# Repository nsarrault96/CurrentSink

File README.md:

# CurrentSink
My version of the Current Sink or Swim project from Contextual Electronics

<br/>

## Component Selection

### Op Amp<br/>
**Part Number:** MCP6002

<br/>

### Voltage Regulator<br/>
**Part Number:** MIC5205

<br/>

### Mosfet<br/>
**Part Number:** STP55FN06L

<br/>

### Heatsink<br/>
**Part Number:** 529702B02500G

<br/>

### Current Sense Resistor<br/>

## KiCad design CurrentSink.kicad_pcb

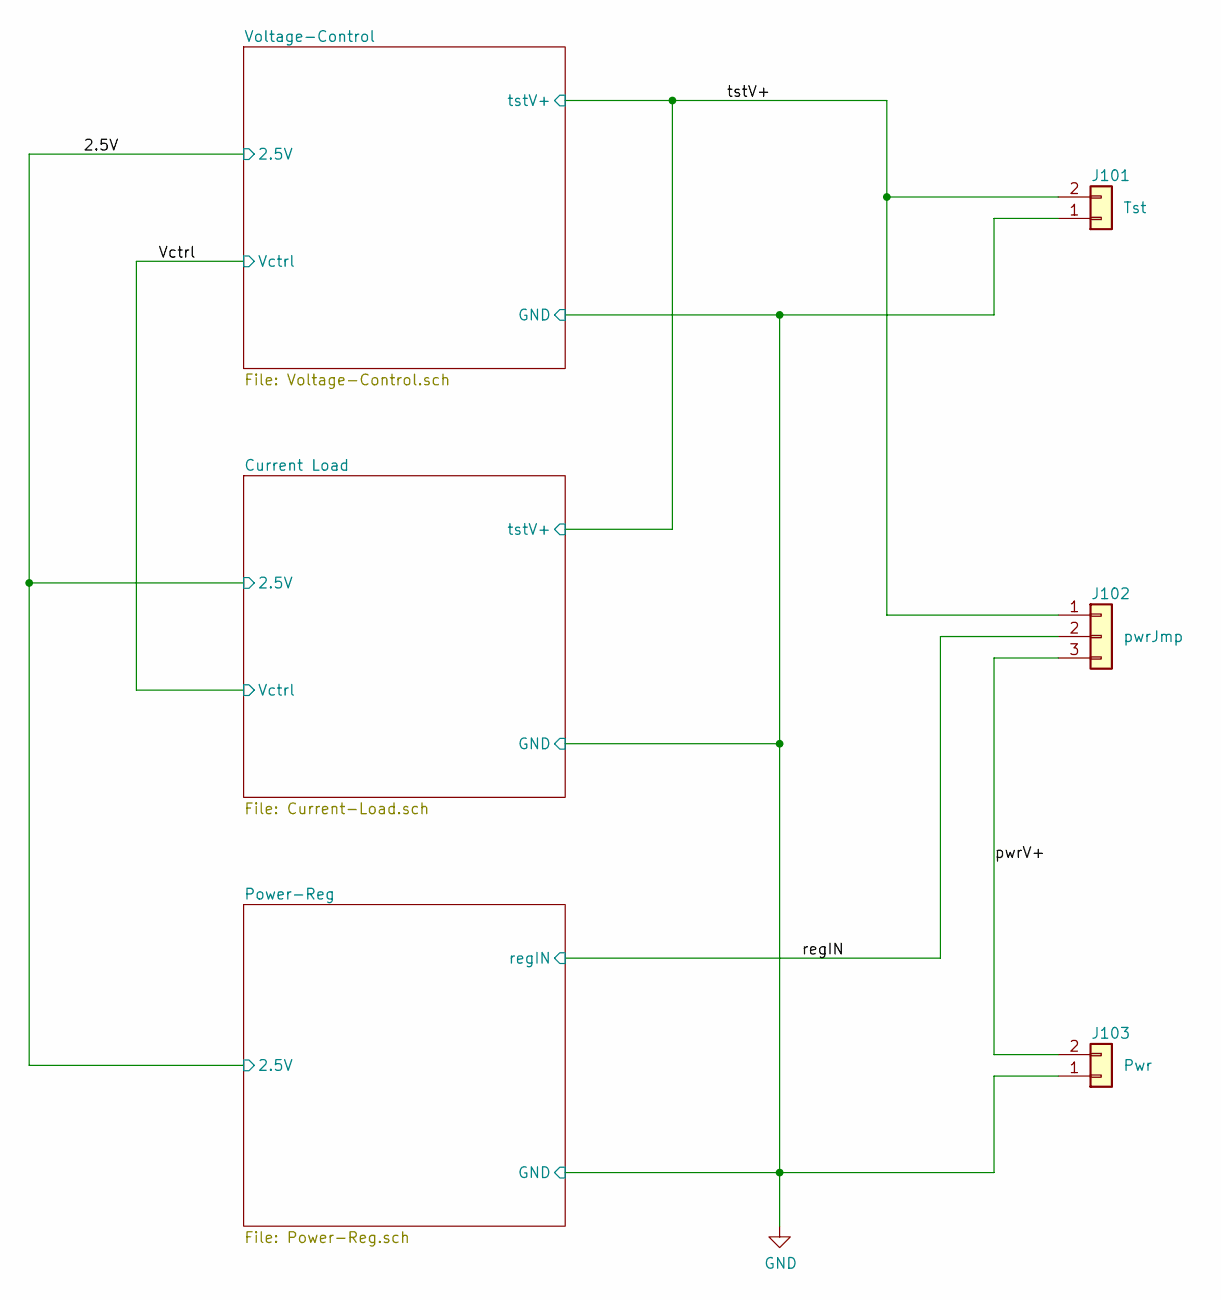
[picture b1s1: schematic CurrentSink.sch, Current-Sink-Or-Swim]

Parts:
J101: Tst; TerminalBlock_Phoenix_PT-1,5-2-3.5-H_1x02_P3.50mm_Horizontal; MPN 1984617
J102: pwrJmp; PinHeader_1x03_P1.27mm_Vertical
J103: Pwr; TerminalBlock_Phoenix_PT-1,5-2-3.5-H_1x02_P3.50mm_Horizontal; MPN 1984617

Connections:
/pwrV+: J102.3, J103.2
/regIN: J102.2; also elsewhere on the board
/tstV+: J101.2, J102.1; also elsewhere on the board
GND: J101.1, J103.1; also elsewhere on the board

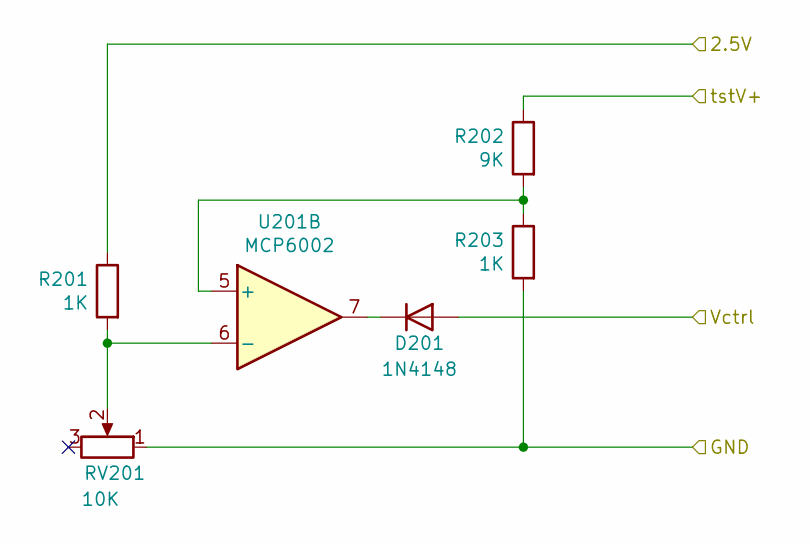
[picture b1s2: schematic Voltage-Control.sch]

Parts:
D201: 1N4148; D_SOD-123
R201, R203: 1K; R_0603_1608Metric_Pad0.98x0.95mm_HandSolder
R202: 9K; R_0603_1608Metric_Pad0.98x0.95mm_HandSolder
RV201: 10K; POT_TTElect_P160KN; MPN P160KN-0QD15B10K
U201: MCP6002; SOIC-8_3.9x4.9mm_P1.27mm; MPN MCP6002T-I/SN

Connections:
/2.5V: R201.1; also elsewhere on the board
/Vctrl: D201.2 (A); also elsewhere on the board
/tstV+: R202.1; also elsewhere on the board
GND: R203.2, RV201.1; also elsewhere on the board
unnamed: D201.1 (K), U201.7
unnamed: R201.2, RV201.2, U201.6 (-)
unnamed: R202.2, R203.1, U201.5 (+)

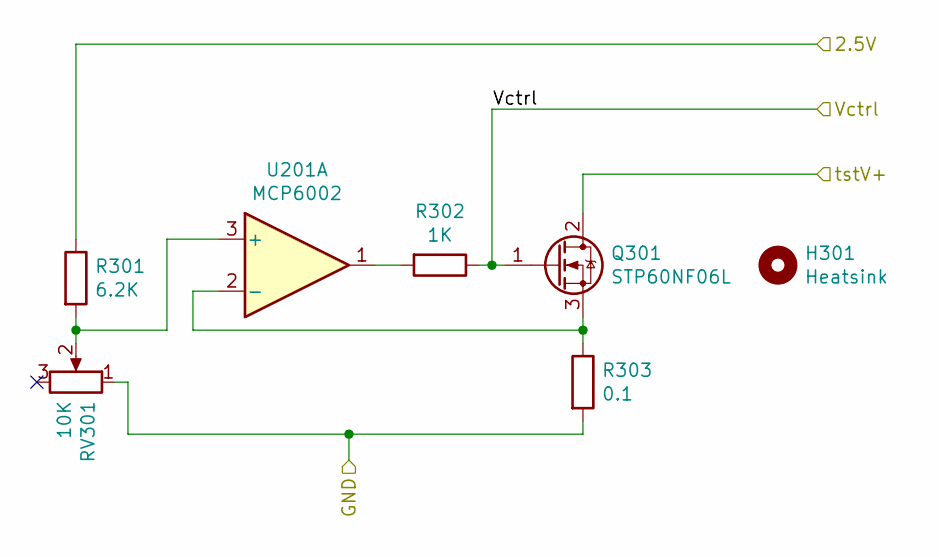
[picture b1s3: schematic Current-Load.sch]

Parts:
H301: Heatsink; MPN 529802B02500G
Q301: STP60NF06L; TO-220-3_Vertical; MPN STP60NF06L
R301: 6.2K; R_0603_1608Metric_Pad0.98x0.95mm_HandSolder
R302: 1K; R_0603_1608Metric_Pad0.98x0.95mm_HandSolder
R303: 0.1; R_2512_6332Metric_Pad1.40x3.35mm_HandSolder; MPN CRA2512-FZ-R100ELF
RV301: 10K; POT_TTElect_P160KN; MPN P160KN-0QD15B10K
U201: MCP6002; SOIC-8_3.9x4.9mm_P1.27mm; MPN MCP6002T-I/SN

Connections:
/2.5V: R301.1; also elsewhere on the board
/Vctrl: Q301.1 (G), R302.1; also elsewhere on the board
/tstV+: Q301.2 (D); also elsewhere on the board
GND: R303.2, RV301.1; also elsewhere on the board
unnamed: Q301.3 (S), R303.1, U201.2 (-)
unnamed: R301.2, RV301.2, U201.3 (+)
unnamed: R302.2, U201.1

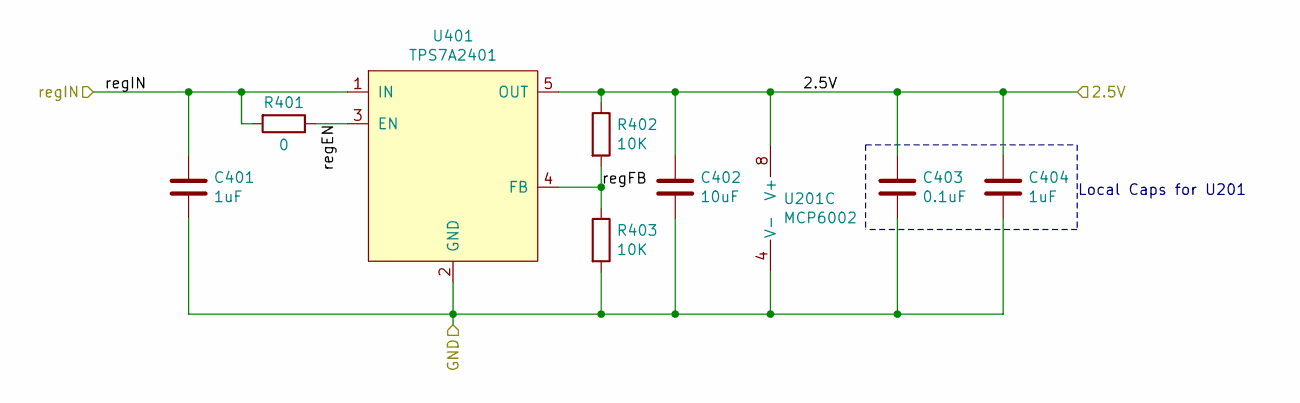
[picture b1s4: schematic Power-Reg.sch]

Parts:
C401, C404: 1uF; C_0603_1608Metric_Pad1.08x0.95mm_HandSolder
C402: 10uF; C_0603_1608Metric_Pad1.08x0.95mm_HandSolder
C403: 0.1uF; C_0603_1608Metric_Pad1.08x0.95mm_HandSolder
R401: 0; R_0603_1608Metric_Pad0.98x0.95mm_HandSolder
R402, R403: 10K; R_0603_1608Metric_Pad0.98x0.95mm_HandSolder
U201: MCP6002; SOIC-8_3.9x4.9mm_P1.27mm; MPN MCP6002T-I/SN
U401: TPS7A2401; SOT-23-5_HandSoldering; MPN TPS7A2401DBVR

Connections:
/2.5V: C402.1, C403.1, C404.1, R402.1, U201.8 (V+), U401.5 (OUT); also elsewhere on the board
/Power-Reg/regEN: R401.1, U401.3 (EN)
/Power-Reg/regFB: R402.2, R403.1, U401.4 (FB)
/regIN: C401.1, R401.2, U401.1 (IN); also elsewhere on the board
GND: C401.2, C402.2, C403.2, C404.2, R403.2, U201.4 (V-), U401.2 (GND); also elsewhere on the board

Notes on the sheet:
Local Caps for U201

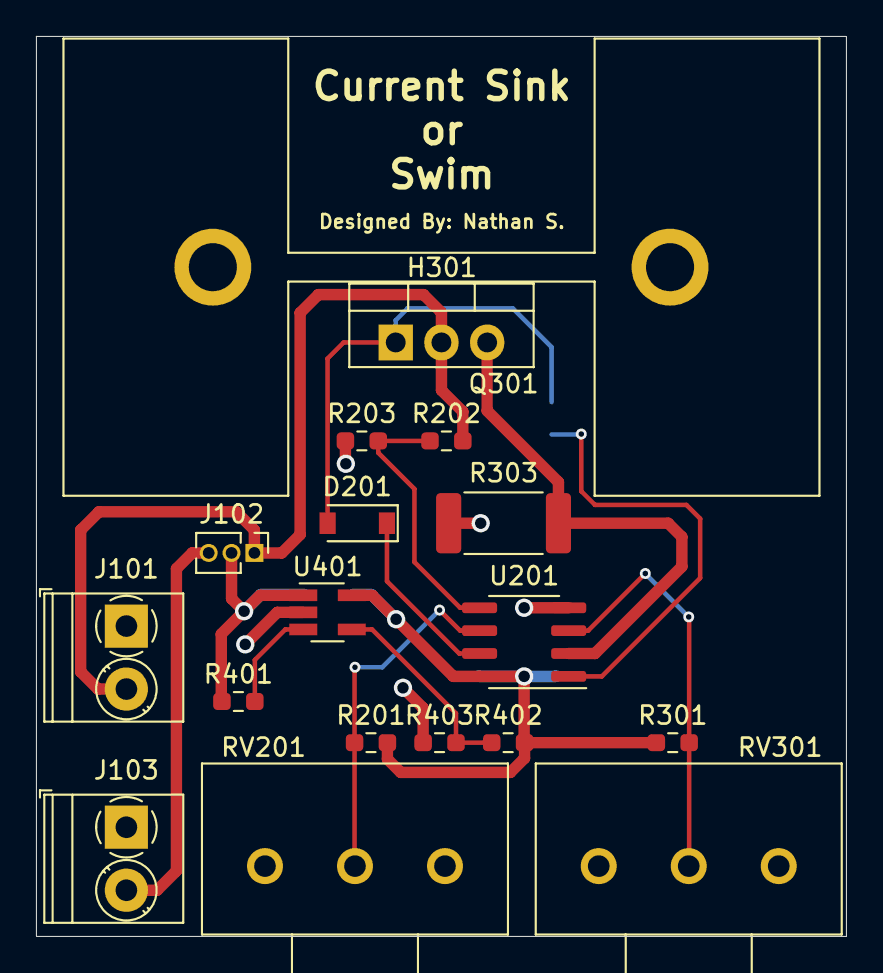
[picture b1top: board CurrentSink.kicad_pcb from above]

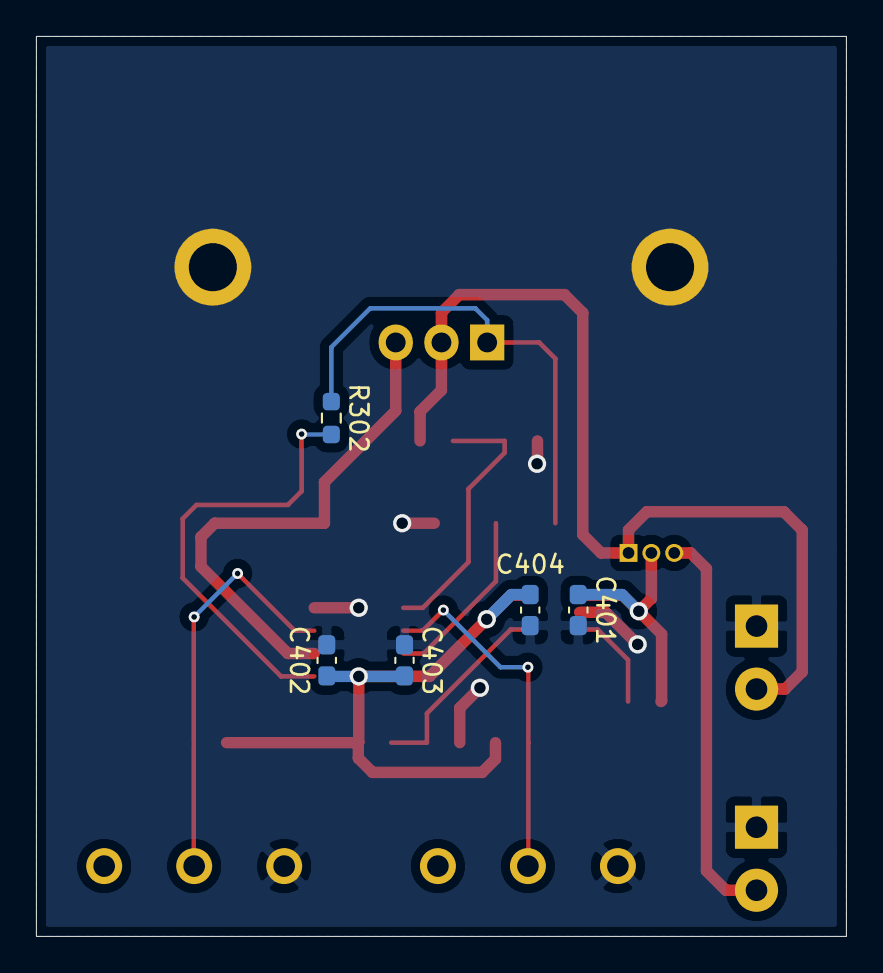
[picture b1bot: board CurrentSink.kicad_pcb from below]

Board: 2 copper layers, 45.0 x 50.0 mm, 23 parts (5 on the bottom side), 14 nets.

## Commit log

2021-01-19 Adding all Kicad files & folders for the project
2021-01-19 Add Component Selection Section
    Initial add of the component selection information to the readme file
2021-01-19 Fix breaks
2021-01-20 Adding the beginning schematic and Datasheets
2021-01-25 Updating the Schematic
2021-02-03 Schematic final version and preliminary footprints
2021-02-03 Adding missing files
2021-02-08 Removing files before creating .gitignore file
2021-02-08 Added .gitignore and heatsink datasheet
2021-02-08 Fixed typo in Current-Load schematic sheet
2021-02-08 Fixing Type in Current-Load schematic again
2021-02-08 Added heatsink to schematic and PCB
2021-02-09 Initial PCB component Placement
2021-03-01 PCB completed with Op-Amp mounted horizontally
2021-03-01 Changed the Op-Amp to be vertical and switched the power input side
2021-03-04 All component placements complete, silk screen cleaned up, and tracks routed. DRC passed.
2021-03-06 Revision A as sent to OSHPark with some MPN updates due to availability
2021-03-06 Revision 1 release
2021-04-04 Fixed reversed Op-Amp for voltage limiting and potentiometer connections to allow for full range of the potentiometer.
